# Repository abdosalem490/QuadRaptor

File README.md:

# QuadRaptor
## MPU6050
This branch contains the source files for all the trials of operating MPU6050 gyroscope and accelerometer.

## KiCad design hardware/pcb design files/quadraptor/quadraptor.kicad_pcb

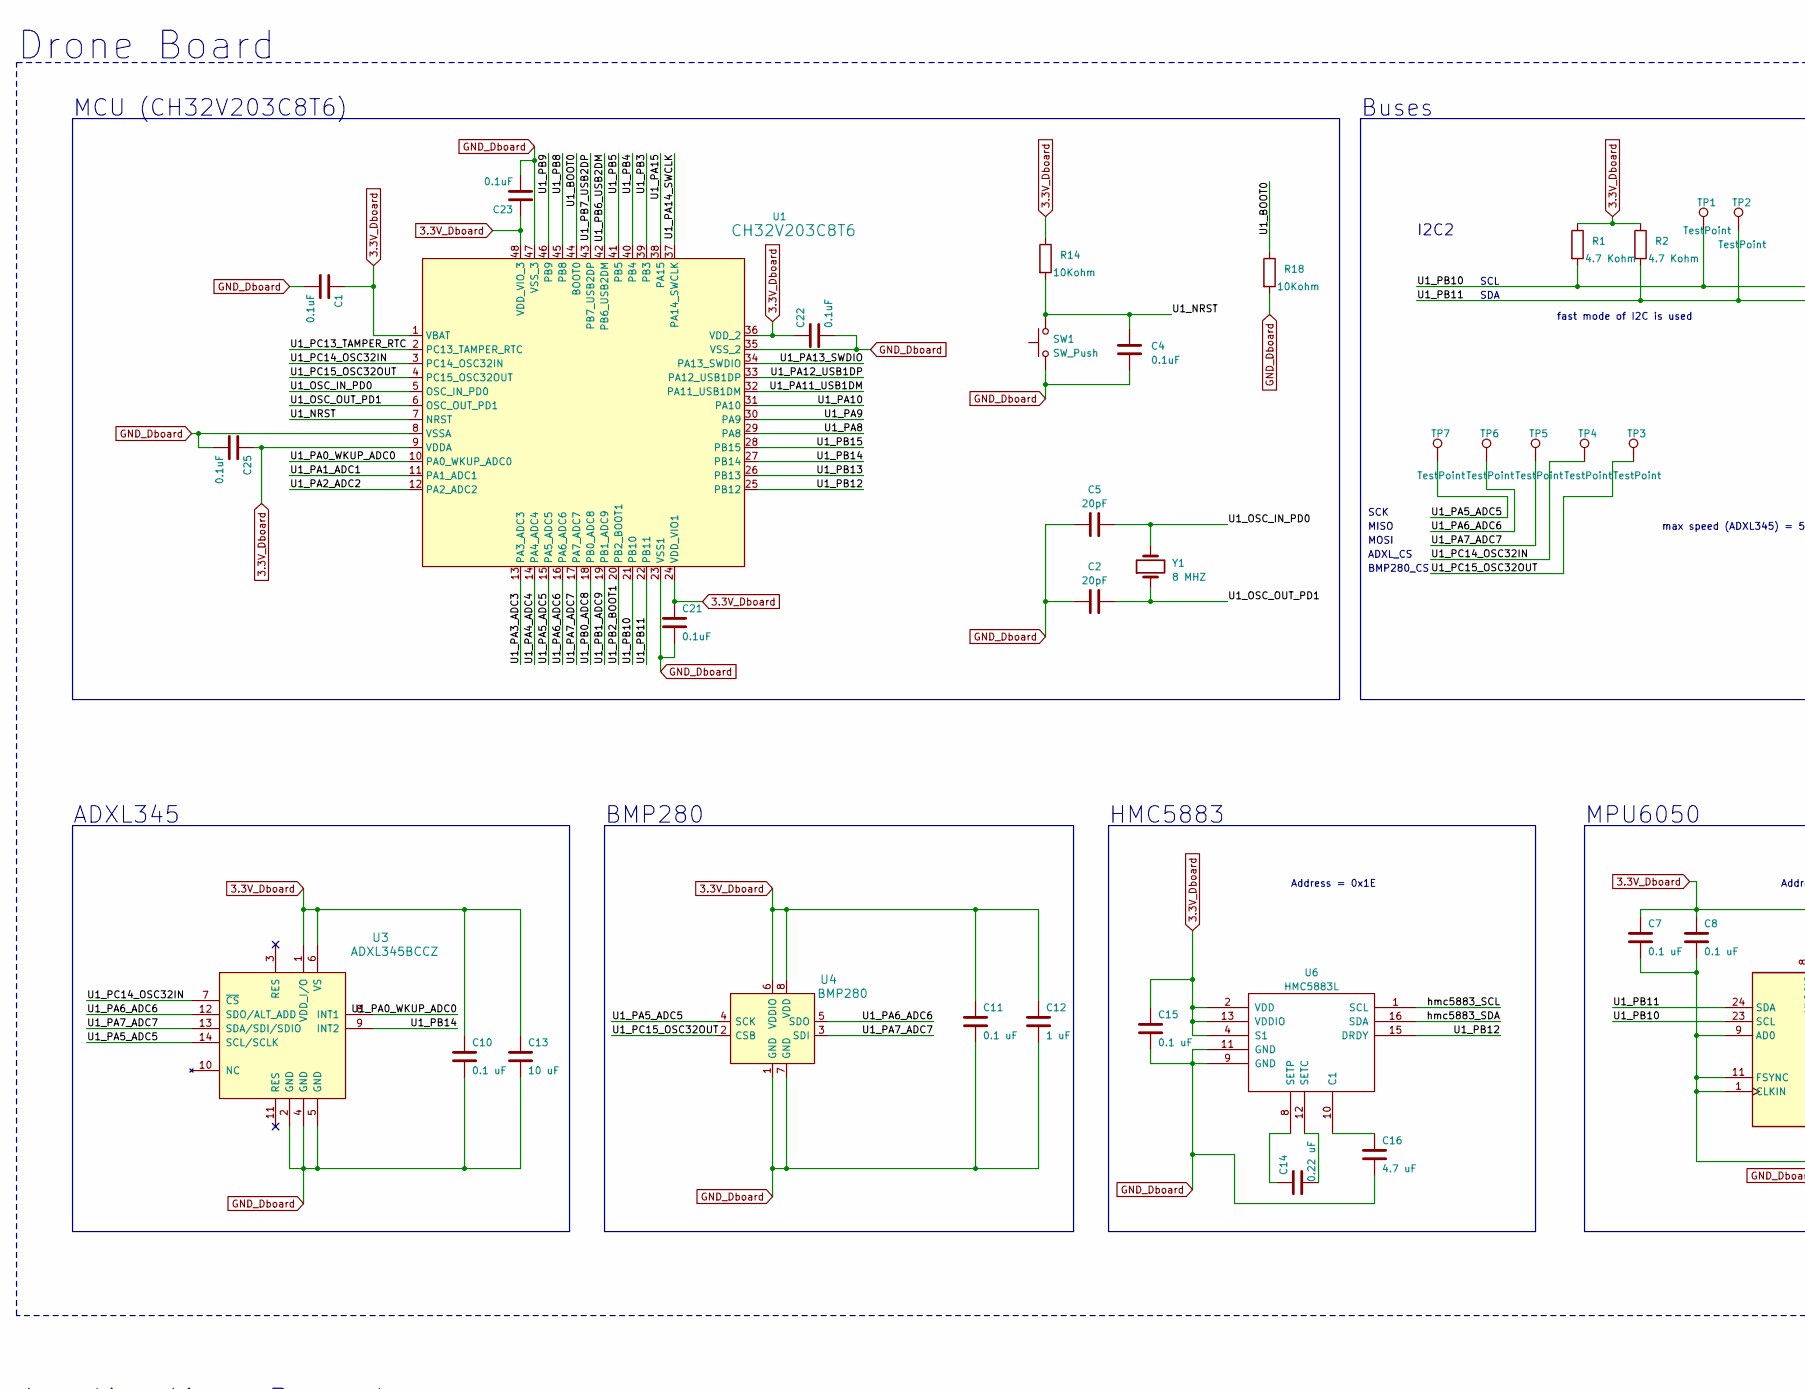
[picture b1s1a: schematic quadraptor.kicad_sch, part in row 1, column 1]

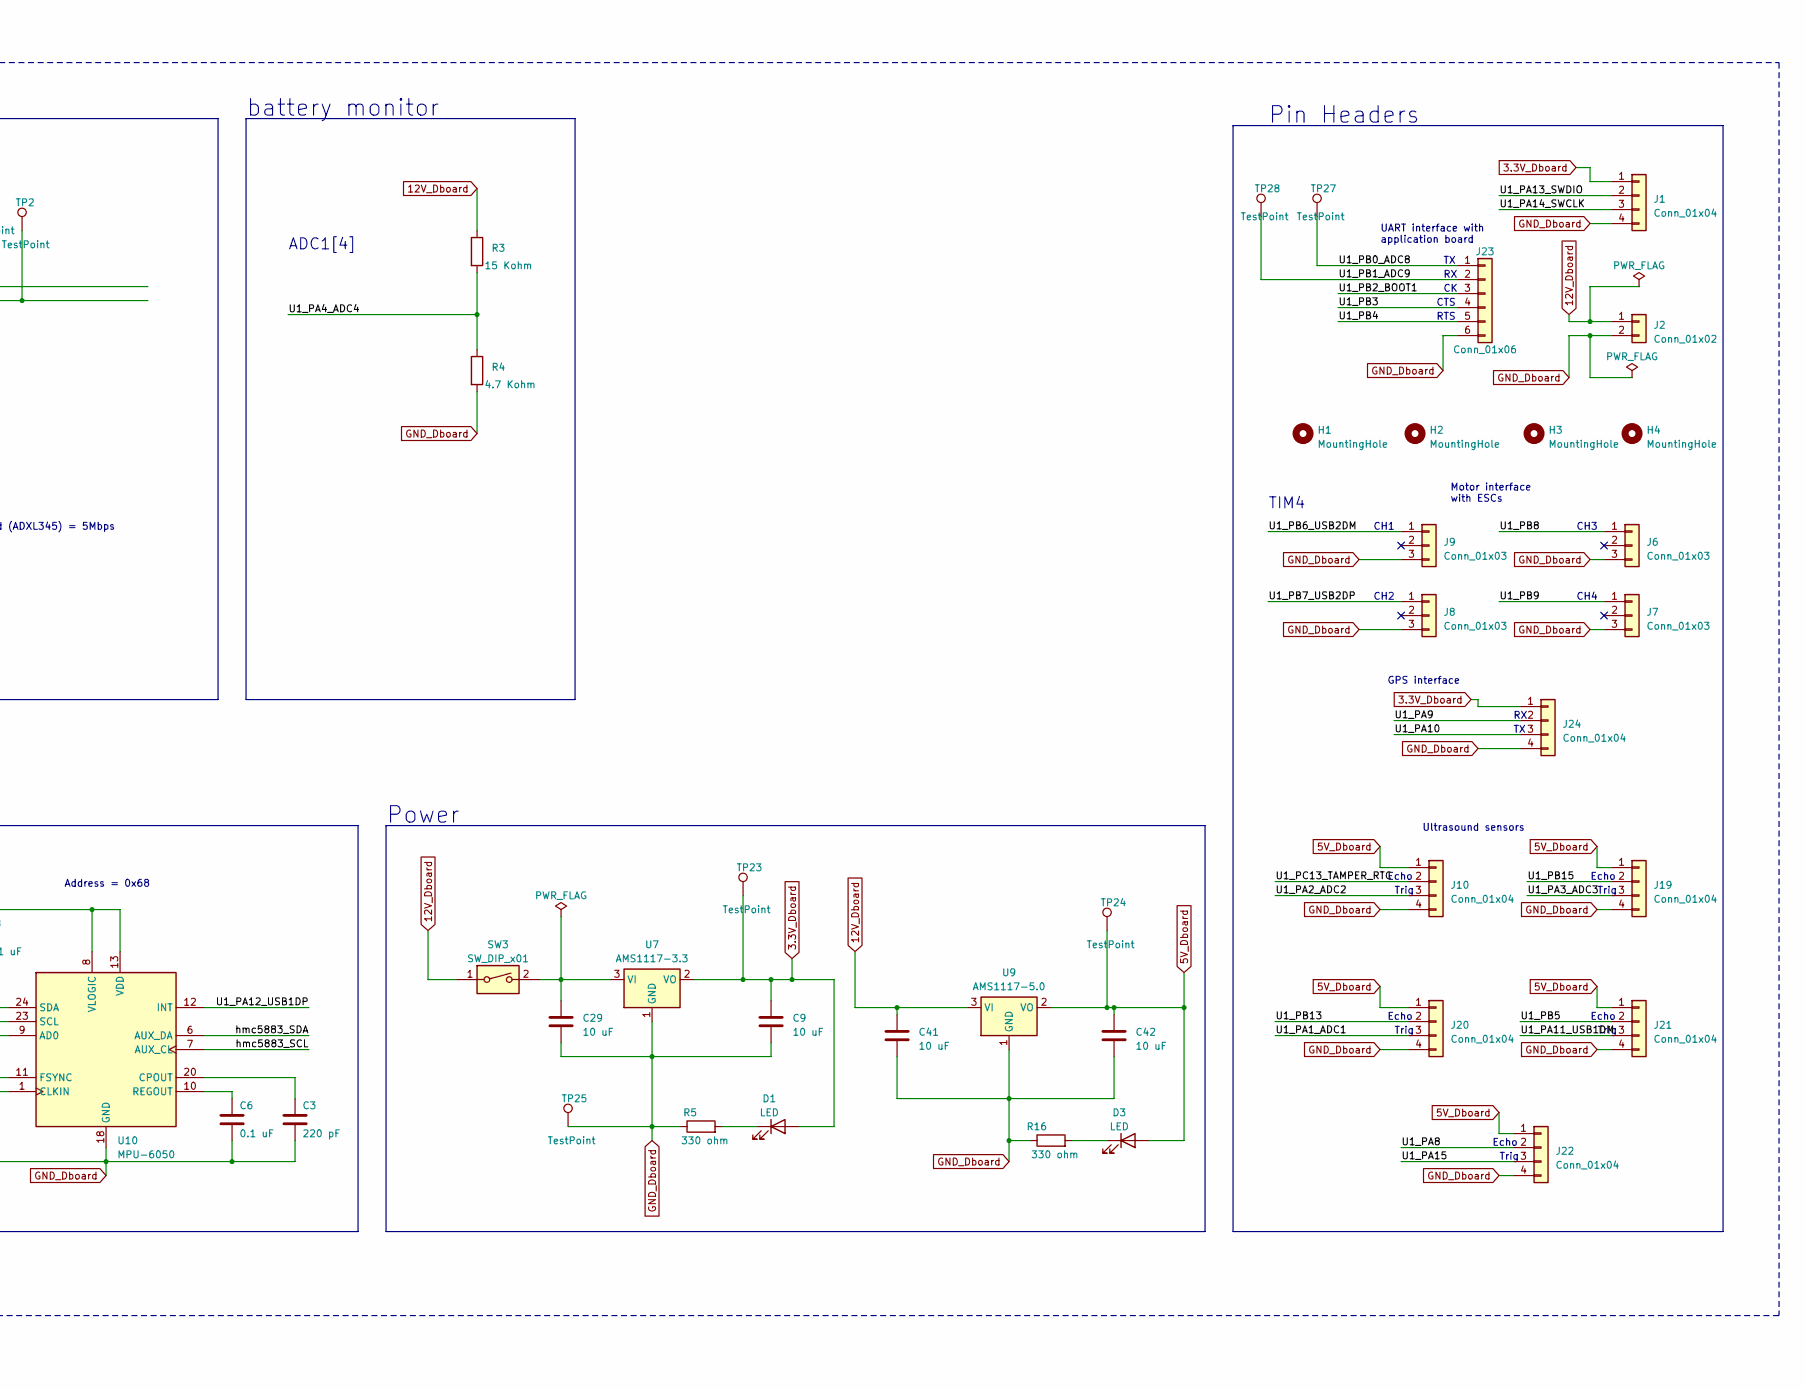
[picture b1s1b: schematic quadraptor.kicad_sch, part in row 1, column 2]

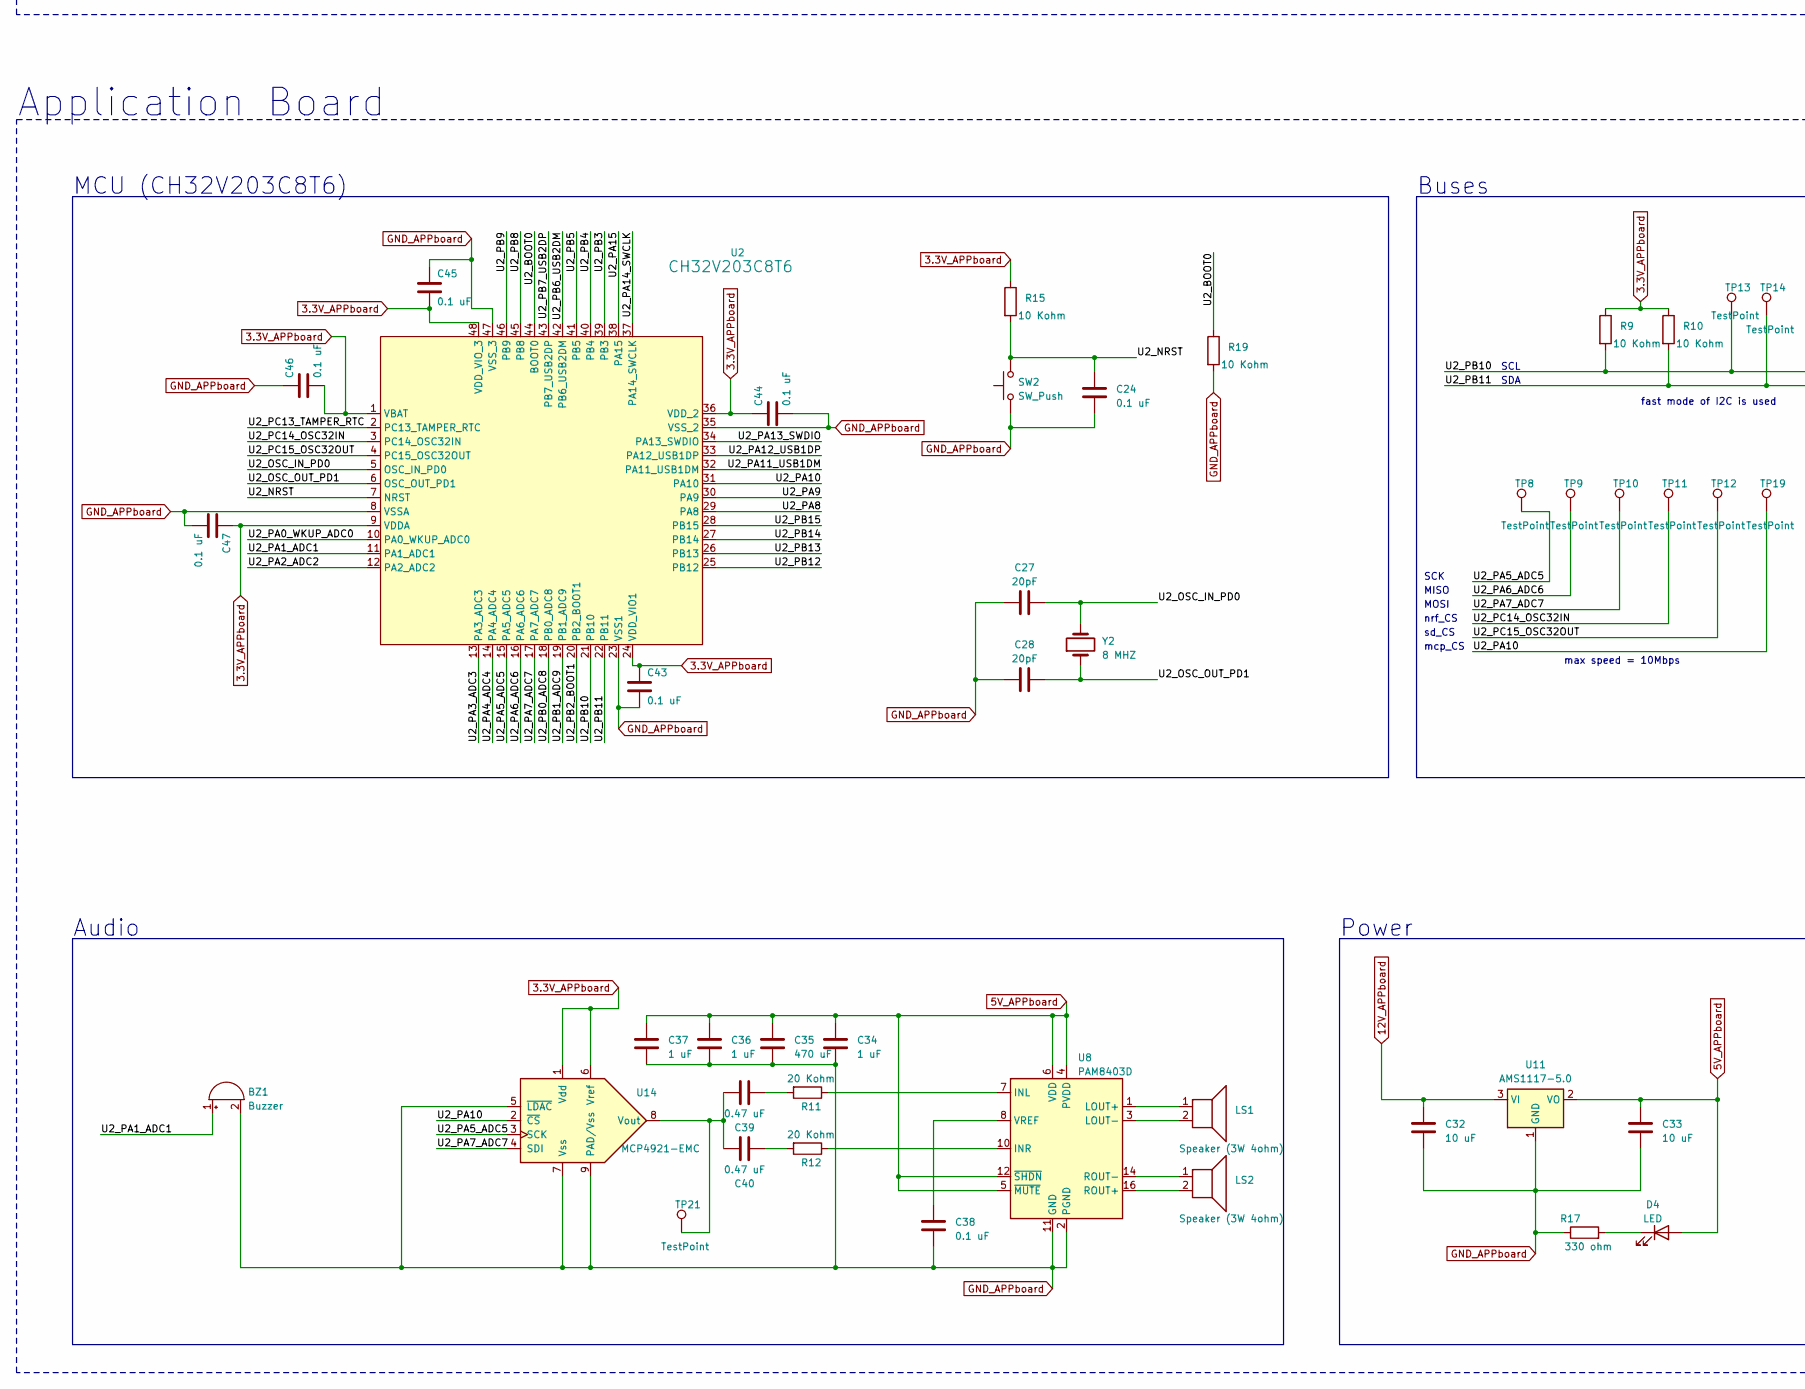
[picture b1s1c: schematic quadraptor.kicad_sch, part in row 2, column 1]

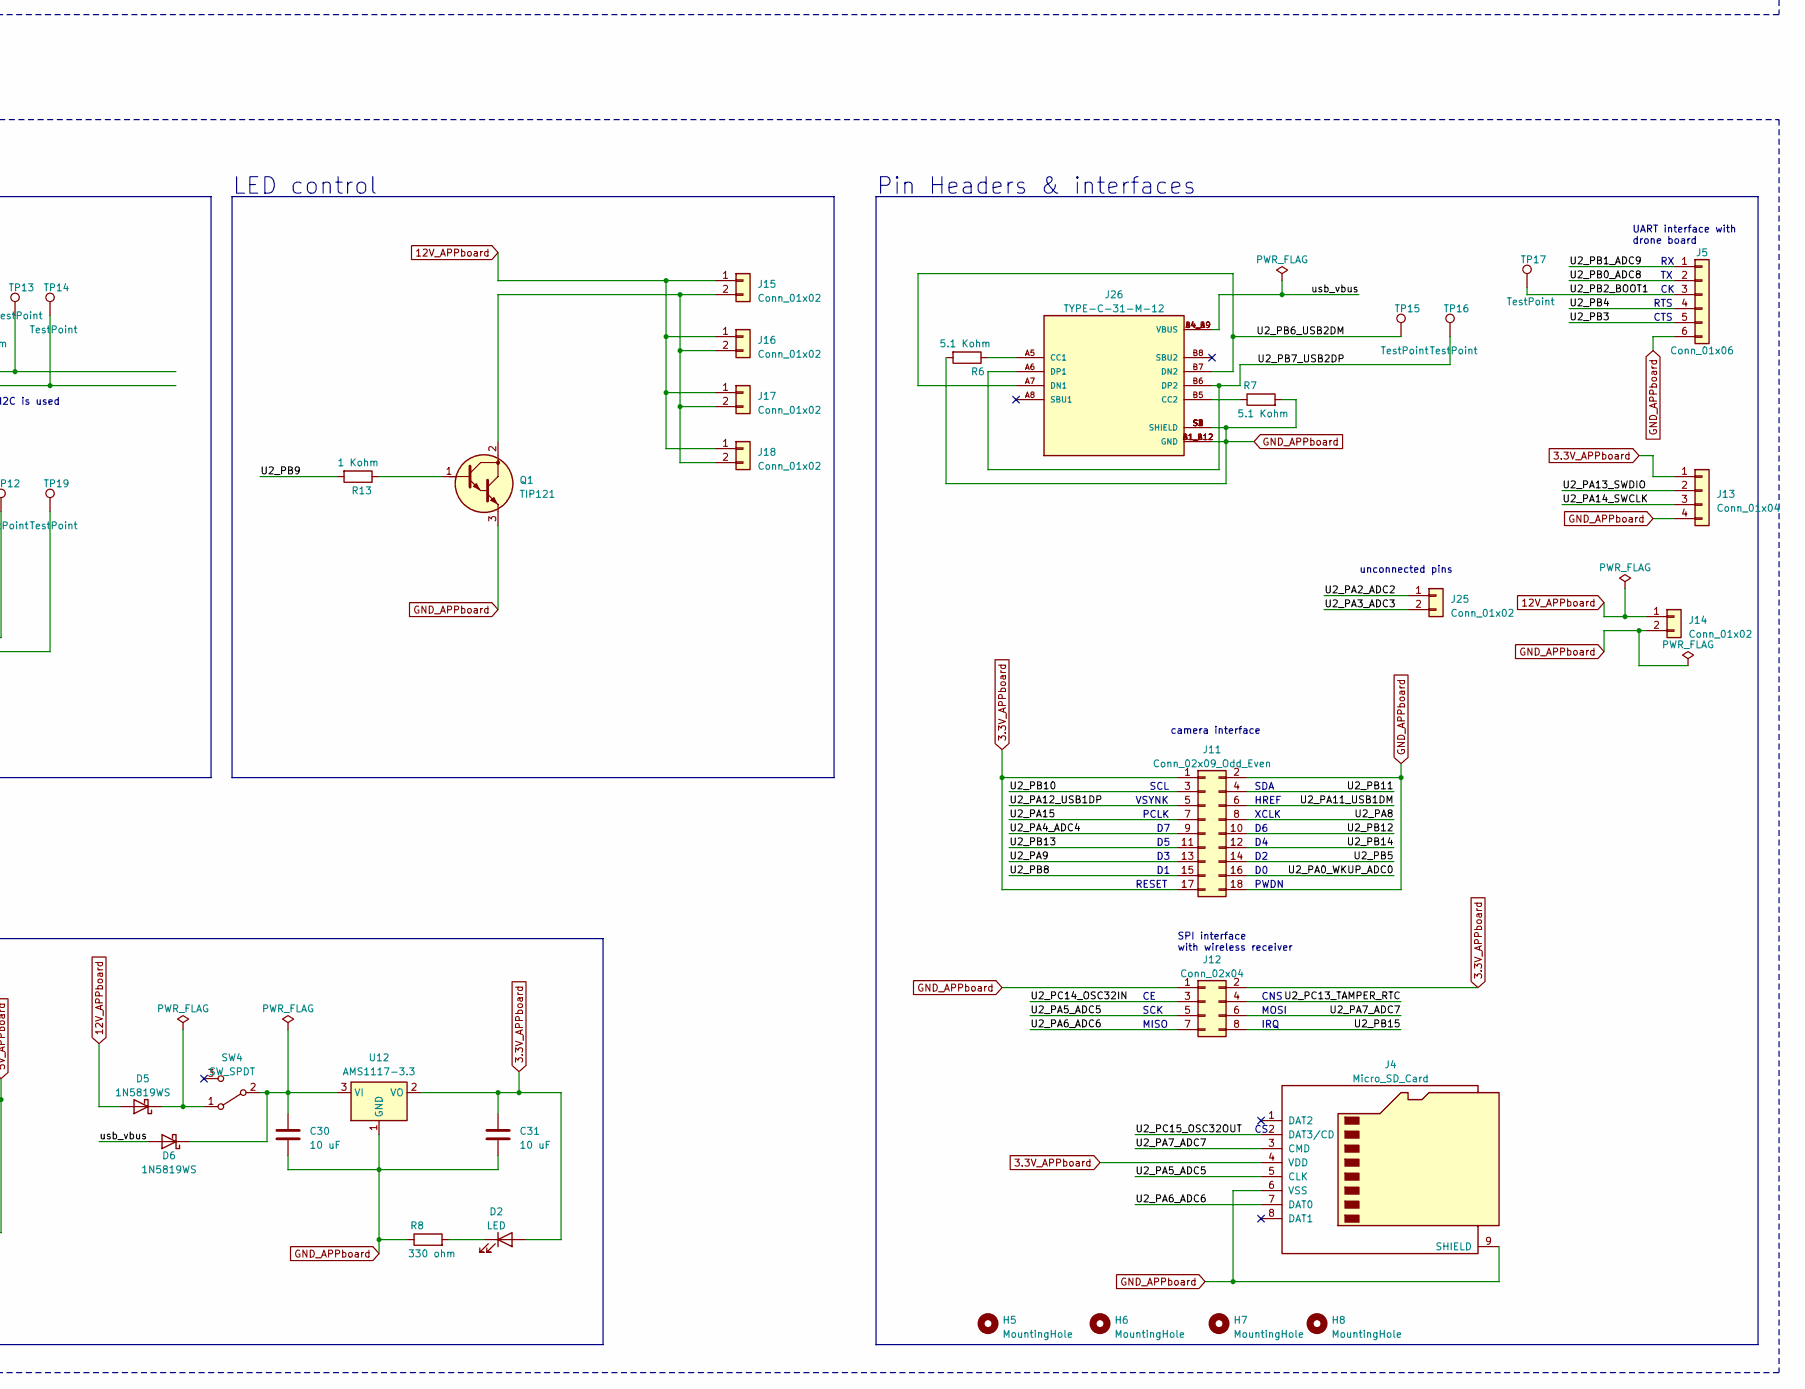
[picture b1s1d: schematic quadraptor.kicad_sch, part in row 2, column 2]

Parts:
BZ1: Buzzer; Buzzer_12x9.5RM7.6
C1, C4, C21, C22, C23, C25: 0.1uF; C_0805_2012Metric_Pad1.18x1.45mm_HandSolder
C2, C5, C27, C28: 20pF; C_0805_2012Metric_Pad1.18x1.45mm_HandSolder
C3: 220 pF; C_0805_2012Metric_Pad1.18x1.45mm_HandSolder
C6, C7, C8, C10, C11, C15, C24, C38, C43, C44, C45, C46, C47: 0.1 uF; C_0805_2012Metric_Pad1.18x1.45mm_HandSolder
C9, C13, C29, C30, C31, C32, C33, C41, C42: 10 uF; C_1206_3216Metric_Pad1.33x1.80mm_HandSolder
C12, C34, C36, C37: 1 uF; C_0805_2012Metric_Pad1.18x1.45mm_HandSolder
C14: 0.22 uF; C_0805_2012Metric_Pad1.18x1.45mm_HandSolder
C16: 4.7 uF; C_0805_2012Metric_Pad1.18x1.45mm_HandSolder
C35: 470 uF; CP_Radial_D5.0mm_P2.00mm
C39, C40: 0.47 uF; C_0805_2012Metric_Pad1.18x1.45mm_HandSolder
D1, D2, D3, D4: LED; LED_0805_2012Metric_Pad1.15x1.40mm_HandSolder
D5, D6: 1N5819WS; D_SMA
H1, H2, H3, H4, H5, H6, H7, H8: MountingHole; MountingHole_3.2mm_M3
J1, J13: Conn_01x04; PinHeader_1x04_P2.54mm_Vertical
J2, J14, J15, J16, J17, J18: Conn_01x02; JST_XH_B2B-XH-A_1x02_P2.50mm_Vertical
J4: Micro_SD_Card; J_SD_Card-micro_socket_A
J5, J23: Conn_01x06; JST_XH_B6B-XH-A_1x06_P2.50mm_Vertical
J6, J7, J8, J9: Conn_01x03; PinHeader_1x03_P2.54mm_Vertical
J10, J19, J20, J21, J22: Conn_01x04; PinSocket_1x04_P2.54mm_Vertical
J11: Conn_02x09_Odd_Even; PinHeader_2x09_P2.54mm_Vertical
J12: Conn_02x04; PinHeader_2x04_P2.54mm_Vertical; Part Number 1-0802FBV0T
J24: Conn_01x04; JST_XH_B4B-XH-A_1x04_P2.50mm_Vertical
J25: Conn_01x02; PinHeader_1x02_P2.54mm_Vertical
J26: TYPE-C-31-M-12; HRO_TYPE-C-31-M-12; PARTREV 2020.12.08
LS1, LS2: Speaker (3W 4ohm); PinHeader_1x02_P2.54mm_Vertical
Q1: TIP121; TO-220-3_Vertical
R1, R2, R4: 4.7 Kohm; R_0805_2012Metric_Pad1.20x1.40mm_HandSolder
R3: 15 Kohm; R_0805_2012Metric_Pad1.20x1.40mm_HandSolder
R5, R8, R16, R17: 330 ohm; R_0603_1608Metric_Pad0.98x0.95mm_HandSolder
R6, R7: 5.1 Kohm; R_0805_2012Metric_Pad1.20x1.40mm_HandSolder
R9, R10, R15, R19: 10 Kohm; R_0805_2012Metric_Pad1.20x1.40mm_HandSolder
R11, R12: 20 Kohm; R_0805_2012Metric_Pad1.20x1.40mm_HandSolder
R13: 1 Kohm; R_0805_2012Metric_Pad1.20x1.40mm_HandSolder
R14, R18: 10Kohm; R_0805_2012Metric_Pad1.20x1.40mm_HandSolder
SW1, SW2: SW_Push; SW_Push_1P1T_NO_6x6mm_H9.5mm
SW3: SW_DIP_x01; SW_EG1218
SW4: SW_SPDT; SW_EG1218
TP1, TP2, TP3, TP4, TP5, TP6, TP7, TP8, TP9, TP10, TP11, TP12, TP13, TP14, TP15, TP16, TP17, TP19, TP21, TP23, TP24, TP25, TP27, TP28: TestPoint; TestPoint_Bridge_Pitch2.54mm_Drill1.0mm
U1, U2: CH32V203C8T6; CH32V203C8T6_LQFP-48_7x7mm_P0.5mm
U3: ADXL345BCCZ; LGA-14_3x5mm_RevA; MPN ADXL345BCCZ; Digi-Key_PN ADXL345BCCZ-ND
U4: BMP280; LGA-8_2x2.5mm_BMP280; MPN BMP280; Digi-Key_PN 828-1064-1-ND
U6: HMC5883L; _HMC5883L
U7, U12: AMS1117-3.3; SOT-223-3_TabPin2
U8: PAM8403D; SOP-16_3.9x9.9mm_P1.27mm
U9, U11: AMS1117-5.0; SOT-223-3_TabPin2
U10: MPU-6050; InvenSense_QFN-24_4x4mm_P0.5mm
U14: MCP4921-EMC; MSOP-8-1EP_3x3mm_P0.65mm_EP1.68x1.88mm
Y1, Y2: 8 MHZ; Crystal_HC18-U_Vertical

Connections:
3.3V_APPboard: C31.1, C43.1, C44.1, C45.2, C46.2, C47.1, D2.2 (A), J4.4 (VDD), J11.1, J11.17, J12.2, J13.1, R9.1, R10.1, R15.1, U2.1 (VBAT), U2.9 (VDDA), U2.24 (VDD_VIO1), U2.36 (VDD_2), U2.48 (VDD_VIO_3), U12.2 (VO), U14.1 (Vdd), U14.6 (Vref)
3.3V_Dboard: C1.1, C7.1, C8.1, C9.1, C10.1, C11.1, C12.1, C13.1, C15.1, C21.1, C22.1, C23.1, C25.1, D1.2 (A), J1.1, J24.1, R1.1, R2.1, R14.1, TP23.1, U1.1 (VBAT), U1.9 (VDDA), U1.24 (VDD_VIO1), U1.36 (VDD_2), U1.48 (VDD_VIO_3), U3.1 (VDD_I/O), U3.6 (VS), U4.6 (VDDIO), U4.8 (VDD), U6.2 (VDD), U6.4 (S1), U6.13 (VDDIO), U7.2 (VO), U10.8 (VLOGIC), U10.13 (VDD)
5V_APPboard: C33.1, C34.1, C35.1, C36.1, C37.1, D4.2 (A), U8.4 (PVDD), U8.5 (~MUTE), U8.6 (VDD), U8.12 (~SHDN), U8.13 (PVDD), U11.2 (VO)
5V_Dboard: C42.1, D3.2 (A), J10.1, J19.1, J20.1, J21.1, J22.1, TP24.1, U9.2 (VO)
12V_APPboard: C32.1, D5.2 (A), J14.1, J15.1, J16.1, J17.1, J18.1, U11.3 (VI)
12V_Dboard: C41.1, J2.1, R3.1, SW3.1, U9.3 (VI)
/U1_BOOT0: R18.1, U1.44 (BOOT0)
/U1_NRST: C4.1, R14.2, SW1.2, U1.7 (NRST)
/U1_OSC_IN_PD0: C5.1, U1.5 (OSC_IN_PD0), Y1.2
/U1_OSC_OUT_PD1: C2.1, U1.6 (OSC_OUT_PD1), Y1.1
/U1_PA0_WKUP_ADC0: U1.10 (PA0_WKUP_ADC0), U3.8 (INT1)
/U1_PA1_ADC1: J20.3, U1.11 (PA1_ADC1)
/U1_PA2_ADC2: J10.3, U1.12 (PA2_ADC2)
/U1_PA3_ADC3: J19.3, U1.13 (PA3_ADC3)
/U1_PA4_ADC4: R3.2, R4.1, U1.14 (PA4_ADC4)
/U1_PA5_ADC5: TP7.1, U1.15 (PA5_ADC5), U3.14 (SCL/SCLK), U4.4 (SCK)
/U1_PA6_ADC6: TP6.1, U1.16 (PA6_ADC6), U3.12 (SDO/ALT_ADD), U4.5 (SDO)
/U1_PA7_ADC7: TP5.1, U1.17 (PA7_ADC7), U3.13 (SDA/SDI/SDIO), U4.3 (SDI)
/U1_PA8: J22.2, U1.29 (PA8)
/U1_PA9: J24.2, U1.30 (PA9)
/U1_PA10: J24.3, U1.31 (PA10)
/U1_PA11_USB1DM: J21.3, U1.32 (PA11_USB1DM)
/U1_PA12_USB1DP: U1.33 (PA12_USB1DP), U10.12 (INT)
/U1_PA13_SWDIO: J1.2, U1.34 (PA13_SWDIO)
/U1_PA14_SWCLK: J1.3, U1.37 (PA14_SWCLK)
/U1_PA15: J22.3, U1.38 (PA15)
/U1_PB0_ADC8: J23.1, TP27.1, U1.18 (PB0_ADC8)
/U1_PB1_ADC9: J23.2, TP28.1, U1.19 (PB1_ADC9)
/U1_PB2_BOOT1: J23.3, U1.20 (PB2_BOOT1)
/U1_PB3: J23.4, U1.39 (PB3)
/U1_PB4: J23.5, U1.40 (PB4)
/U1_PB5: J21.2, U1.41 (PB5)
/U1_PB6_USB2DM: J9.1, U1.42 (PB6_USB2DM)
/U1_PB7_USB2DP: J8.1, U1.43 (PB7_USB2DP)
/U1_PB8: J6.1, U1.45 (PB8)
/U1_PB9: J7.1, U1.46 (PB9)
/U1_PB10: R1.2, TP1.1, U1.21 (PB10), U10.23 (SCL)
/U1_PB11: R2.2, TP2.1, U1.22 (PB11), U10.24 (SDA)
/U1_PB12: U1.25 (PB12), U6.15 (DRDY)
/U1_PB13: J20.2, U1.26 (PB13)
/U1_PB14: U1.27 (PB14), U3.9 (INT2)
/U1_PB15: J19.2, U1.28 (PB15)
/U1_PC13_TAMPER_RTC: J10.2, U1.2 (PC13_TAMPER_RTC)
/U1_PC14_OSC32IN: TP4.1, U1.3 (PC14_OSC32IN), U3.7 (~CS)
/U1_PC15_OSC32OUT: TP3.1, U1.4 (PC15_OSC32OUT), U4.2 (CSB)
/U2_BOOT0: R19.1, U2.44 (BOOT0)
/U2_NRST: C24.1, R15.2, SW2.2, U2.7 (NRST)
/U2_OSC_IN_PD0: C27.1, U2.5 (OSC_IN_PD0), Y2.2
/U2_OSC_OUT_PD1: C28.1, U2.6 (OSC_OUT_PD1), Y2.1
/U2_PA0_WKUP_ADC0: J11.16, U2.10 (PA0_WKUP_ADC0)
/U2_PA1_ADC1: BZ1.1 (-), U2.11 (PA1_ADC1)
/U2_PA2_ADC2: J25.1, U2.12 (PA2_ADC2)
/U2_PA3_ADC3: J25.2, U2.13 (PA3_ADC3)
/U2_PA4_ADC4: J11.9, U2.14 (PA4_ADC4)
/U2_PA5_ADC5: J4.5 (CLK), J12.5, TP8.1, U2.15 (PA5_ADC5), U14.3 (SCK)
/U2_PA6_ADC6: J4.7 (DAT0), J12.7, TP9.1, U2.16 (PA6_ADC6)
/U2_PA7_ADC7: J4.3 (CMD), J12.6, TP10.1, U2.17 (PA7_ADC7), U14.4 (SDI)
/U2_PA8: J11.8, U2.29 (PA8)
/U2_PA9: J11.13, U2.30 (PA9)
/U2_PA10: TP19.1, U2.31 (PA10), U14.2 (~CS)
/U2_PA11_USB1DM: J11.6, U2.32 (PA11_USB1DM)
/U2_PA12_USB1DP: J11.5, U2.33 (PA12_USB1DP)
/U2_PA13_SWDIO: J13.2, U2.34 (PA13_SWDIO)
/U2_PA14_SWCLK: J13.3, U2.37 (PA14_SWCLK)
/U2_PA15: J11.7, U2.38 (PA15)
/U2_PB0_ADC8: J5.2, U2.18 (PB0_ADC8)
/U2_PB1_ADC9: J5.1, U2.19 (PB1_ADC9)
/U2_PB2_BOOT1: J5.3, TP17.1, U2.20 (PB2_BOOT1)
/U2_PB3: J5.5, U2.39 (PB3)
/U2_PB4: J5.4, U2.40 (PB4)
/U2_PB5: J11.14, U2.41 (PB5)
/U2_PB6_USB2DM: J26.A7 (DN1), J26.B7 (DN2), TP15.1, U2.42 (PB6_USB2DM)
/U2_PB7_USB2DP: J26.A6 (DP1), J26.B6 (DP2), TP16.1, U2.43 (PB7_USB2DP)
/U2_PB8: J11.15, U2.45 (PB8)
/U2_PB9: R13.2, U2.46 (PB9)
/U2_PB10: J11.3, R9.2, TP13.1, U2.21 (PB10)
/U2_PB11: J11.4, R10.2, TP14.1, U2.22 (PB11)
/U2_PB12: J11.10, U2.25 (PB12)
/U2_PB13: J11.11, U2.26 (PB13)
/U2_PB14: J11.12, U2.27 (PB14)
/U2_PB15: J12.8, U2.28 (PB15)
/U2_PC13_TAMPER_RTC: J12.4, U2.2 (PC13_TAMPER_RTC)
/U2_PC14_OSC32IN: J12.3, TP11.1, U2.3 (PC14_OSC32IN)
/U2_PC15_OSC32OUT: J4.2 (DAT3/CD), TP12.1, U2.4 (PC15_OSC32OUT)
/hmc5883_SCL: U6.1 (SCL), U10.7 (AUX_CL)
/hmc5883_SDA: U6.16 (SDA), U10.6 (AUX_DA)
/usb_vbus: D6.2 (A), J26.A4_B9 (VBUS), J26.B4_A9 (VBUS)
GND_APPboard: BZ1.2 (+), C24.2, C27.2, C28.2, C30.2, C31.2, C32.2, C33.2, C34.2, C35.2, C36.2, C37.2, C38.2, C43.2, C44.2, C45.1, C46.1, C47.2, J4.6 (VSS), J4.9 (SHIELD), J5.6, J11.2, J11.18, J12.1, J13.4, J14.2, J26.A1_B12 (GND), J26.B1_A12 (GND), J26.S1 (SHIELD), J26.S2 (SHIELD), J26.S3 (SHIELD), J26.S4 (SHIELD), Q1.3 (E), R6.2, R7.2, R8.1, R17.1, R19.2, SW2.1, U2.8 (VSSA), U2.23 (VSS1), U2.35 (VSS_2), U2.47 (VSS_3), U8.2 (PGND), U8.11 (GND), U8.15 (PGND), U11.1 (GND), U12.1 (GND), U14.5 (~LDAC), U14.7 (Vss), U14.9 (PAD/Vss)
GND_Dboard: C1.2, C2.2, C3.2, C4.2, C5.2, C6.2, C7.2, C8.2, C9.2, C10.2, C11.2, C12.2, C13.2, C15.2, C16.2, C21.2, C22.2, C23.2, C25.2, C29.2, C41.2, C42.2, J1.4, J2.2, J6.3, J7.3, J8.3, J9.3, J10.4, J19.4, J20.4, J21.4, J22.4, J23.6, J24.4, R4.2, R5.1, R16.1, R18.2, SW1.1, TP25.1, U1.8 (VSSA), U1.23 (VSS1), U1.35 (VSS_2), U1.47 (VSS_3), U3.2 (GND), U3.4 (GND), U3.5 (GND), U4.1 (GND), U4.7 (GND), U6.9 (GND), U6.11 (GND), U7.1 (GND), U9.1 (GND), U10.1 (CLKIN), U10.9 (AD0), U10.11 (FSYNC), U10.18 (GND)
unnamed: C39.2, R11.2
unnamed: C40.2, R12.2
unnamed: D1.1 (K), R5.2
unnamed: D2.1 (K), R8.2
unnamed: D3.1 (K), R16.2
unnamed: D4.1 (K), R17.2
unnamed: D5.1 (K), SW4.1 (A)
unnamed: C30.1, D6.1 (K), SW4.2 (B), U12.3 (VI)
unnamed: J15.2, J16.2, J17.2, J18.2, Q1.2 (C)
unnamed: J26.A5 (CC1), R6.1
unnamed: J26.B5 (CC2), R7.1
unnamed: Q1.1 (B), R13.1
unnamed: C16.1, U6.10 (C1)
unnamed: C14.2, U6.12 (SETC)
unnamed: C14.1, U6.8 (SETP)
unnamed: C29.1, SW3.2, U7.3 (VI)
unnamed: R11.1, U8.7 (INL)
unnamed: R12.1, U8.10 (INR)
unnamed: LS1.1, U8.1 (LOUT+)
unnamed: LS1.2, U8.3 (LOUT-)
unnamed: LS2.2, U8.16 (ROUT+)
unnamed: LS2.1, U8.14 (ROUT-)
unnamed: C38.1, U8.8 (VREF)
unnamed: C3.1, U10.20 (CPOUT)
unnamed: C6.1, U10.10 (REGOUT)
unnamed: C39.1, C40.1, TP21.1, U14.8 (Vout)

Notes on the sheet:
UART interface with application board
SCL
XCLK
CH3
battery monitor
RTS
Buses
BMP280_CS
MISO
mcp_CS
CTS
Audio
RESET
HREF
Power
CH2
CNS
Ultrasound sensors
SPI interface with wireless receiver
UART interface with drone board
fast mode of I2C is used
camera interface
Echo
SCK
Drone Board
Address = 0x1E
sd_CS
GPS interface
HMC5883
IRQ
MPU6050
ADC1[4]
MCU (CH32V203C8T6)
SDA
Pin Headers & interfaces
BMP280
Address = 0x68
Motor interface with ESCs
ADXL345
I2C2

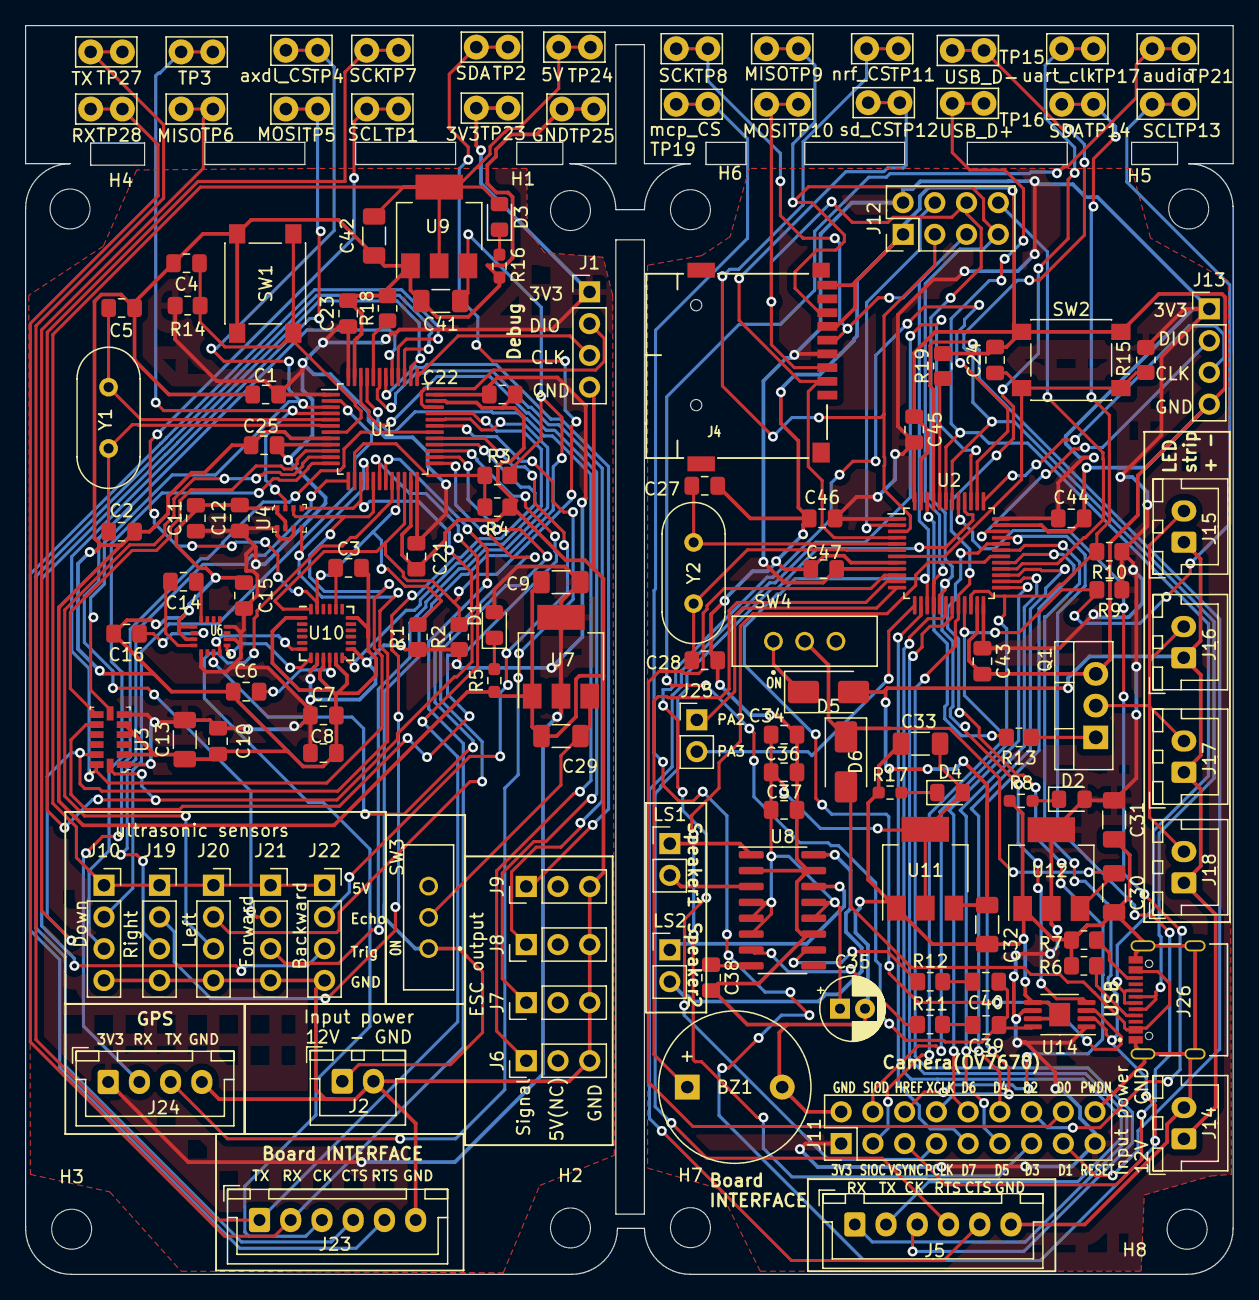
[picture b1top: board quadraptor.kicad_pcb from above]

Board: 2 copper layers, 96.6 x 100.0 mm, 146 parts (0 on the bottom side), 115 nets.

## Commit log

2024-02-02 [ADD]: initial remote control code
2024-02-02 [ADD]: ch32 resources
2024-02-08 [ADD]: sensor datasheets and added some extra schematics
2024-02-14 gyroscope wrapper functions
2024-02-15 [UPDATE]: initial schematic and pin assignments
2024-02-18 [UPDATE]: complete initial code for the remote control
2024-02-23 [UPDATE]: completed initial PCB routing and design
2024-03-01 [ADD]: test code for PWM and ADC
2024-03-09 [UPDATE]: reverted back pcb file of kicad
2024-03-18 Clean main branch #01
2024-03-18 Gyro on Arduino Uno
2024-03-18 Gyro on ch32v203 [spaghetti]
2024-03-18 Revert "Gyro on ch32v203 [spaghetti]"
    This reverts commit eccbb314c89edc53b56926315120a9abed4ca834.
2024-03-19 Gyro on ch32v203 [wrapper]
2024-03-19 master transmit mode macro
2024-03-19 gyro api [no config]
2024-03-19 Explanatory comments
2024-03-22 Move gcvt out of gyro signals
2024-03-22 MPU6050 driver v1.0 [gyro]
2024-03-23 Gyro calibration
2024-03-23 MPU6050 driver v1.0 [accel]
2024-03-31 Two function interface
2024-03-31 std math functions working
2024-03-31 1d kalman (pitch and roll)
2024-05-18 [UPDATE]: create the skeleton project from the drone board
2024-05-18 [UPDATE]: configured FreeRTOS config file
2024-05-18 [UPDATE]: solved an error caused by freeRTOS config file
2024-05-20 [UPDATE]: initial configuration of pins
2024-05-22 [ADD]: Queues initial creation
2024-05-22 [ADD]: queue add function
2024-05-24 [UPDATE]: changed clock value of PCLK1 to be 144 MHZ instead of 72 MHZ and added some configurations to the SPI of ADXL345
2024-06-11 [ADD]: init function for ADXL345
2024-06-12 [ADD]: read acc functionality for ADXL345 and wraepper
2024-06-12 [UPDATE]: ADXL345 is now integrated and working fine
2024-06-12 HMC5883L very noisy
2024-06-13 [UPDATE]: * IMPORTANT NOTE: ADXL345 isn't working, it's either a problem with SPI pins routing or the chip is fake * I bought 2 ADXL345 modules, one from AliExpress and the other from free-electronic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
2024-06-13 [UPDATE]: successfully integrated MPU6050
2024-06-14 [UPDATE]: integrated initial SensorFusion with kalman filter
2024-06-14 [UPDATE]: integrated HMC5883L code and corrected direction of readings according to the placement of the ICs on the PCB
2024-06-14 [UPDATE]: correct orientation of pitch and roll as they were reversed
2024-06-15 [ADD]: ESCs drivers code
2024-06-17 HMC5883L outputs YAW
2024-06-17 IMU wo altitude
2024-06-18 [UPDATE]: added initial task communication code (to be tested)
2024-06-18 [ADD]: initial code for App board
2024-06-18 [UPDATE]: deleted testcodes folder
2024-06-18 [TEMP]
2024-06-18 [UPDATE]: initial integration with HMC5883 yaw measurment
2024-06-18 Yaw calculated
2024-06-18 HMC fused with Gyro
2024-06-18 [UPDATE]: yaw is fused final1
2024-06-20 Create BME280
    bme driver first version
2024-06-20 bme first version
    not trial_1
2024-06-21 [UPADTE]: solved initial problems with UART comm
2024-06-21 [UPDATE]: still there is a problem with UART
2024-06-22 [UPDATE]: I give up, I have a deadline to meet and it seems the interrupts is messing with freeRTOS functionality so I will just make use of freeRTOS idle task to receive data when there is any.
2024-06-22 [UPDATE]: communication between the 2 boards is now working correctly but with a polling approach (not using interrupts)
2024-06-22 [TEMP]: temporary commit for switching
2024-06-22 [UPDATE]: BMP280 is integrated successfully but the IC was burnt because of applying pressur on it :(
2024-06-24 [UPDATE]: integrated RC with app board
2024-06-25 [UPDATE]: dtone baord can receive from remote control but there is a bug in sending
2024-06-25 [UPDATE]: drone board can now send info to the remote control
2024-06-25 [ADD]: 3d model for ultrasonic holder
2024-06-25 Comment fix
2024-06-25 [UPDATE]: changed delay in drone board to use MCAL_WRAPPER_DelayUS instead of MCAL_WRAPPER_DelayMS
2024-06-25 [TEMP]: test push
2024-06-26 PID & MMA
2024-06-26 Barometer altitude
2024-06-26 Matrix utility
2024-06-26 Removed unnecessary include
2024-06-26 Altitude fused
2024-06-26 [UPDATE]: solved build errors
2024-06-26 [UPDATE]: a problem with timer interrupt, trying to check if the chip is fake or not
2024-06-28 [UPDATE]: ultrasonic sensor is now working with TIM1 without halting the processor
2024-06-28 [UPDATE]: battery charge is now working
2024-06-28 [TEMP]: temp update
2024-06-28 [UPDATE]: remote control can now start and stop the drone
2024-06-28 [UPDATE]: test code for motors
2024-06-29 [UPDATE]: mapped the values of the remote control to correct values and added a limit to these values in the app board.
2024-06-30 [UPDATE]: changed yaw used in pid to be yaw rate instead
2024-06-30 [UPDATE]: changed the motors speed update way
2024-06-30 NaN fix
2024-06-30 Motor math model
2024-06-30 kalman-filter-2d quickfix
2024-06-30 Kalman filter quickfix 1.1
2024-06-30 [UPDATE]: initial pid parameter
2024-07-01 [UPDATE]: PID block code modified with upper and lower bounds for error integral along with adding weights for blocks
2024-07-02 [UPDATE]: fixed a bug in MCAL_WRAPEPR_TIM4_PWM_OUT
2024-07-02 [UPDATE]: 1st flight trial
2024-07-03 [UPDATE]: 2nd trial 03/07/2024
2024-07-04 [UPDATE]: first tuned pitch and roll PID values
2024-07-05 [update]: better values for roll and pitch
2024-07-05 [UPDATE]: better values for yaw with roll and pitch
2024-07-06 VerticalVelocity
2024-07-08 Sensor put into the loop
2024-07-08 Rate control added
2024-07-08 [UPDATE]: temp commit
2024-07-08 [UPDATE]: temp updata
2024-07-08 [UPDATE]: temp update
2024-07-08 [UPDATE]: correct code
2024-07-08 thrust
2024-07-14 mpu refactored
2024-07-14 hmc refactored
2024-07-14 hmc documented
2024-07-14 mpu documented
2024-07-14 Sesnor fusion cleaned
2024-07-14 last commit
2024-07-15 kalman minor edit
2024-07-15 Create test.c
    first driver
2024-07-15 Create test.c
    gpio
2024-07-15 Create ss
2024-07-15 Create s
2024-07-15 modelling
2024-07-15 [UPDATE]: final commit
2024-07-20 [UPDATE]: added the presentation file
